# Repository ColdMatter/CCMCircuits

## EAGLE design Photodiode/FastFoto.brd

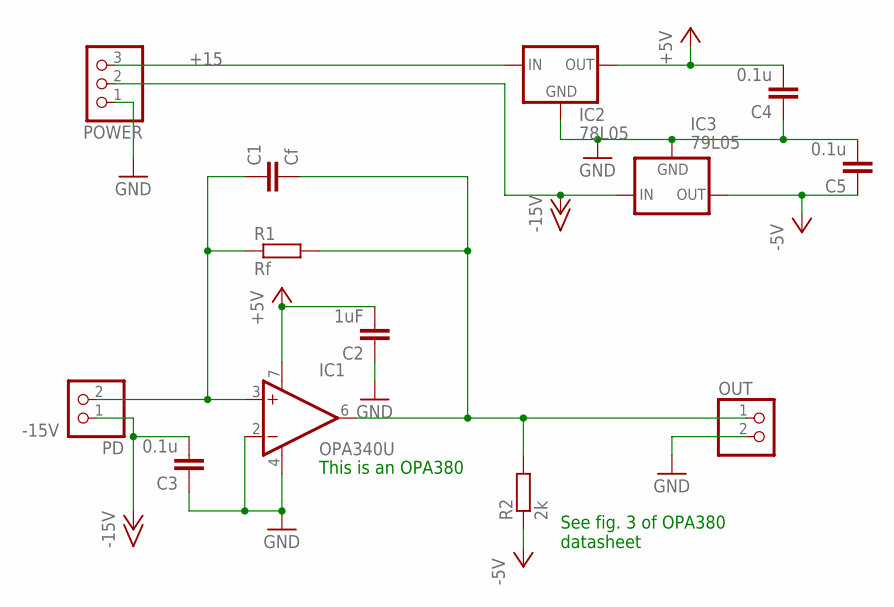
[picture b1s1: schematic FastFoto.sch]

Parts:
C1: Cf; C050-030X075
C2: 1uF; C050-030X075
C3, C4, C5: 0.1u; C050-030X075
IC1: OPA340U; SO08
IC2: 78L05; 78LXX
IC3: 79L05; 79LXX
OUT: PINHD-1X2; 1X02
PD: PINHD-1X2; 1X02
POWER: PINHD-1X3; 1X03
R1: Rf; 0204/7
R2: 2k; 0204/7

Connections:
+5V: C2.2, C4.2, IC1.7 (V+), IC2.OUT
+15: IC2.IN, POWER.3
-5V: C5.1, IC3.OUT, R2.1
-15V: C3.2, IC3.IN, PD.1, POWER.2
GND: C2.1, C3.1, C4.1, C5.2, IC1.2 (-IN), IC1.4 (V-), IC2.GND, IC3.GND, OUT.2, POWER.1
unnamed: C1.2, IC1.6 (OUT), OUT.1, R1.2, R2.2
unnamed: C1.1, IC1.3 (+IN), PD.2, R1.1

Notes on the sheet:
This is an OPA380
See fig. 3 of OPA380 datasheet

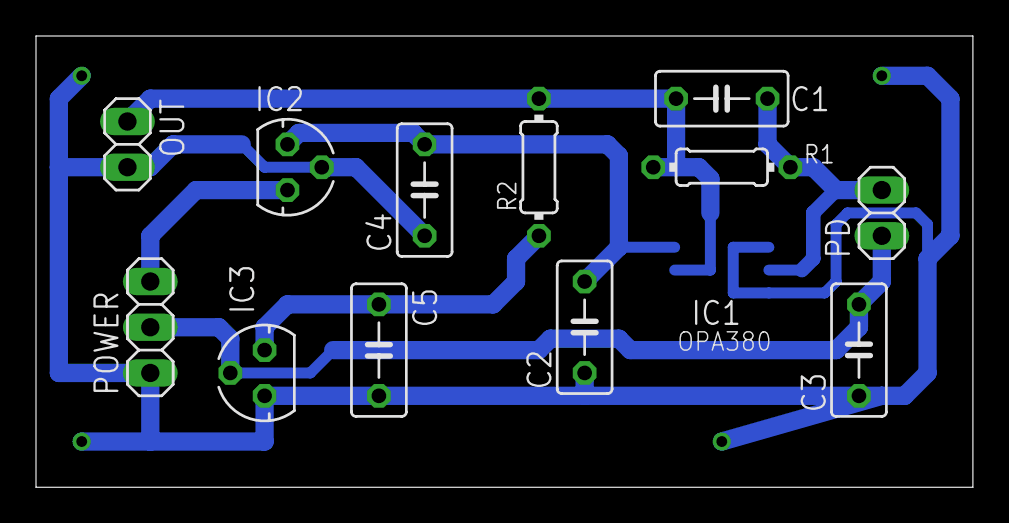
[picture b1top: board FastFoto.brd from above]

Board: 2 copper layers, 52.0 x 25.1 mm, 13 parts (1 on the bottom side), 7 nets.
